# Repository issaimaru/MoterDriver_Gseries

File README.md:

# MoterDriver_Gseries (通称:MOEL53)
- A面

- B面

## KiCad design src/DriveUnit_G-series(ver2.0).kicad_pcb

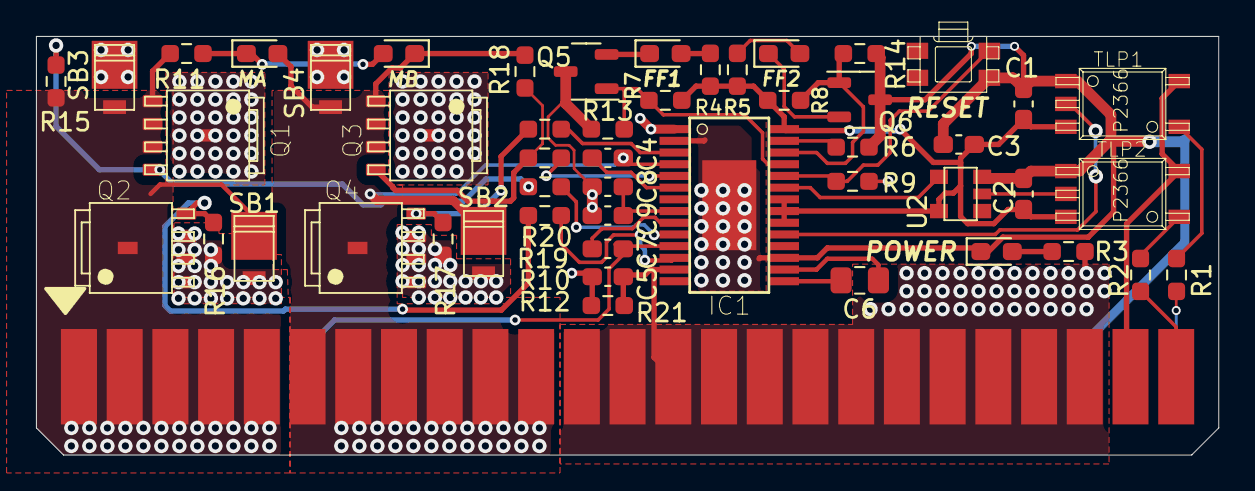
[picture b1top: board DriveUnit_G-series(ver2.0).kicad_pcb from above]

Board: 2 copper layers, 65.7 x 23.3 mm, 52 parts (1 on the bottom side), 36 nets.

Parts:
C1, C2, C3, C4, C5, C7, C8: 100n; C_0603_1608Metric_Pad1.08x0.95mm_HandSolder
C6: 470n; C_0805_2012Metric_Pad1.18x1.45mm_HandSolder
C9: 2.2u; C_0603_1608Metric_Pad1.08x0.95mm_HandSolder
C10: 220u; U2-R_NCH
EDGE1: 10046971-019LF
FF1, FF2: LED; LED_0603_1608Metric_Pad1.05x0.95mm_HandSolder
IC1: A3921
MA: LED; LED_0603_1608Metric_Pad1.05x0.95mm_HandSolder
MB: LED; LED_0603_1608Metric_Pad1.05x0.95mm_HandSolder
POWER: LED; LED_0603_1608Metric_Pad1.05x0.95mm_HandSolder
Q1, Q2, Q3, Q4: SQJA16EP-T1_GE3
Q5, Q6: Q_NPN_BCE; SOT-23-3
R1, R2, R4, R5: 200; R_0603_1608Metric_Pad0.98x0.95mm_HandSolder
R3, R11: 1k; R_0603_1608Metric_Pad0.98x0.95mm_HandSolder
R6: 3k; R_0603_1608Metric_Pad0.98x0.95mm_HandSolder
R7, R8, R9, R15, R16, R17, R18, R21: 10k; R_0603_1608Metric_Pad0.98x0.95mm_HandSolder
R10, R12, R19, R20: 10; R_0603_1608Metric_Pad0.98x0.95mm_HandSolder
R13, R14: 100k; R_0603_1608Metric_Pad0.98x0.95mm_HandSolder
RESET: THAF01-NC-R
SB1, SB2, SB3, SB4: V2P22LHM3/H; V2P22LHM3_H
TLP1, TLP2: TLP2366
U2: TC7S14F

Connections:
/DIR: IC1.19 (PHASE), TLP1.5 (VOUT)
/DIR_IN: EDGE1.P$26 (P26), R1.2
/FF1: IC1.25 (FF1), Q5.1 (B), R7.1, R13.2
/FF2: IC1.26 (FF2), Q6.1 (B), R8.1, R14.1
/GHA: IC1.10 (GHA), R10.2
/GHB: IC1.5 (GHB), R19.1
/GLA: IC1.12 (GLA), R12.2
/GLB: IC1.3 (GLB), R20.1
/GND_IN: EDGE1.P$24 (P24), TLP1.3 (CATHODE), TLP2.3 (CATHODE)
/PWM: IC1.23 (PWMH), U2.OUT (O)
/PWM_IN: EDGE1.P$25 (P25), R2.2
/RESET: IC1.24 (RESET), R9.2, RESET.3
/SA: C7.2, EDGE1.P$1 (P1), EDGE1.P$2 (P2), EDGE1.P$3 (P3), EDGE1.P$4 (P4), EDGE1.P$5 (P5), EDGE1.P$45 (P45), EDGE1.P$46 (P46), EDGE1.P$47 (P47), EDGE1.P$48 (P48), EDGE1.P$49 (P49), EDGE1.P$50 (P50), IC1.11 (SA), Q1.S1 (S), Q1.S2 (S), Q1.S3 (S), Q2.D, R11.2, R15.1, SB1.C, SB3.A
/SB: C4.2, EDGE1.P$6 (P6), EDGE1.P$7 (P7), EDGE1.P$8 (P8), EDGE1.P$9 (P9), EDGE1.P$10 (P10), EDGE1.P$11 (P11), EDGE1.P$40 (P40), EDGE1.P$41 (P41), EDGE1.P$42 (P42), EDGE1.P$43 (P43), EDGE1.P$44 (P44), IC1.4 (SB), MA.2 (A), MB.1 (K), Q3.S1 (S), Q3.S2 (S), Q3.S3 (S), Q4.D, R18.1, SB2.C, SB4.A
/V5: C1.2, C2.2, C3.2, IC1.20 (V5), IC1.21 (SR), IC1.22 (PWML), IC1.28 (VDSTH), R4.2, R5.2, R7.2, R8.2, TLP1.6 (VCC), TLP2.6 (VCC), U2.VCC
GND: C1.1, C2.1, C3.1, C5.1, C8.1, C9.1, C10.2, EDGE1.P$28 (P28), EDGE1.P$29 (P29), EDGE1.P$30 (P30), EDGE1.P$31 (P31), EDGE1.P$32 (P32), EDGE1.P$33 (P33), EDGE1.P$34 (P34), EDGE1.P$35 (P35), EDGE1.P$36 (P36), EDGE1.P$37 (P37), EDGE1.P$38 (P38), EDGE1.P$39 (P39), IC1.2 (LSS), IC1.17 (GND), IC1.PAD (GND), POWER.1 (K), Q2.S1 (S), Q2.S2 (S), Q2.S3 (S), Q4.S1 (S), Q4.S2 (S), Q4.S3 (S), Q5.3 (E), Q6.3 (E), R6.1, R13.1, R14.2, R16.1, R17.1, R21.1, RESET.1, SB1.A, SB2.A, TLP1.4 (GND), TLP2.4 (GND), U2.GND
unnamed: MA.1 (K), MB.2 (A), R11.1
unnamed: POWER.2 (A), R3.1
unnamed: FF1.2 (A), R4.1
unnamed: FF1.1 (K), Q5.2 (C)
unnamed: FF2.2 (A), R5.1
unnamed: FF2.1 (K), Q6.2 (C)
unnamed: C7.1, IC1.9 (CA)
unnamed: C4.1, IC1.6 (CB)
unnamed: C6.1, IC1.16 (CP1)
unnamed: C6.2, IC1.15 (CP2)
unnamed: IC1.27 (RDEAD), R6.2
unnamed: C8.2, C9.2, IC1.8 (VREG)
unnamed: Q1.G, R10.1, R15.2
unnamed: Q2.G, R12.1, R16.2
unnamed: Q3.G, R18.2, R19.2
unnamed: Q4.G, R17.2, R20.2
unnamed: R1.1, TLP1.1 (ANODE)
unnamed: R2.1, TLP2.1 (ANODE)
unnamed: TLP2.5 (VOUT), U2.IN (I)
VCC: C5.2, C10.1, EDGE1.P$12 (P12), EDGE1.P$13 (P13), EDGE1.P$14 (P14), EDGE1.P$15 (P15), EDGE1.P$16 (P16), EDGE1.P$17 (P17), EDGE1.P$18 (P18), EDGE1.P$19 (P19), EDGE1.P$20 (P20), EDGE1.P$21 (P21), EDGE1.P$22 (P22), EDGE1.P$23 (P23), IC1.1 (VDRAIN), IC1.13 (VBB), Q1.D, Q3.D, R3.2, R9.1, R21.2, SB3.C, SB4.C

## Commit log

2023-10-31 [add]回路図完成
2023-11-01 [add]配線途中まで
2023-11-01 [add]電源ライン以外の配線完了
2023-11-01 [complete]配線完了
2023-11-01 [wip]DRC全通過完了
2023-11-01 :tada:完成
2023-11-02 [fix]部品配置微修正
2023-11-15 add production file
2023-11-15 add Azusa_solidasm file
